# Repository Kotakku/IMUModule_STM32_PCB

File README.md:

# IMUModule_STM32_PCB

KiCad project to reproduce the contents of the following paper

H. Kamata, M. Kimishima, T. Sawada, Y. Suga, H. Takeda, K. Yamashita, and S. Mitani, MEMS Gyro Array Employing Array Signal Processing for Interference and Outlier Suppression, IEEE Inertial 2020, Hiroshima, Japan

## Firmware
[IMUModule_G473RC](https://github.com/Kotakku/IMUModule_G473RC)

## Board spec
- STM32G473RC
- LSM6DSR (x32)

## Requirements
- KiCad 8
- [KiCAD JLCPCB tools](https://github.com/bouni/kicad-jlcpcb-tools) (for JLCPCB PCBA)

## Production files
Use the files in ```jlcpcb/production_files```
- ```GERBER-IMUModule_STM32.zip```
- ```CPL-IMUModule_STM32.csv```
- ```BOM-IMUModule_STM32.csv```

## Images

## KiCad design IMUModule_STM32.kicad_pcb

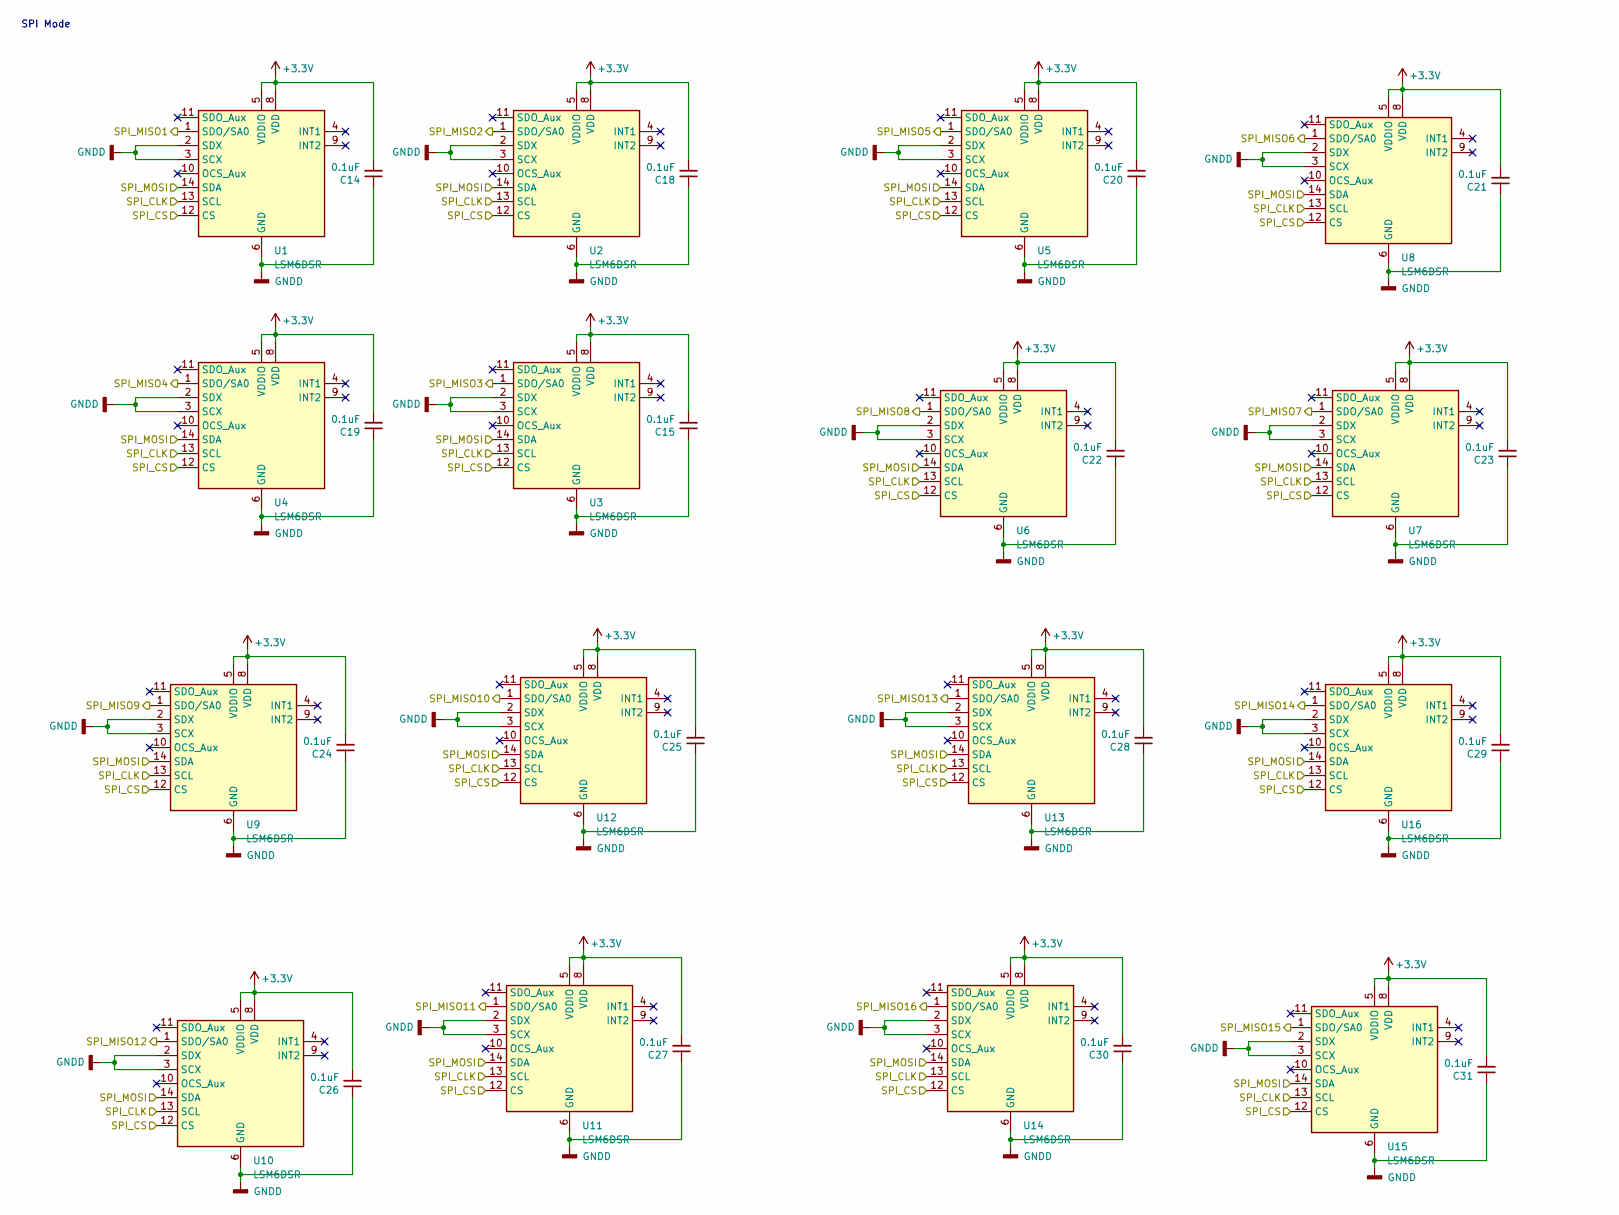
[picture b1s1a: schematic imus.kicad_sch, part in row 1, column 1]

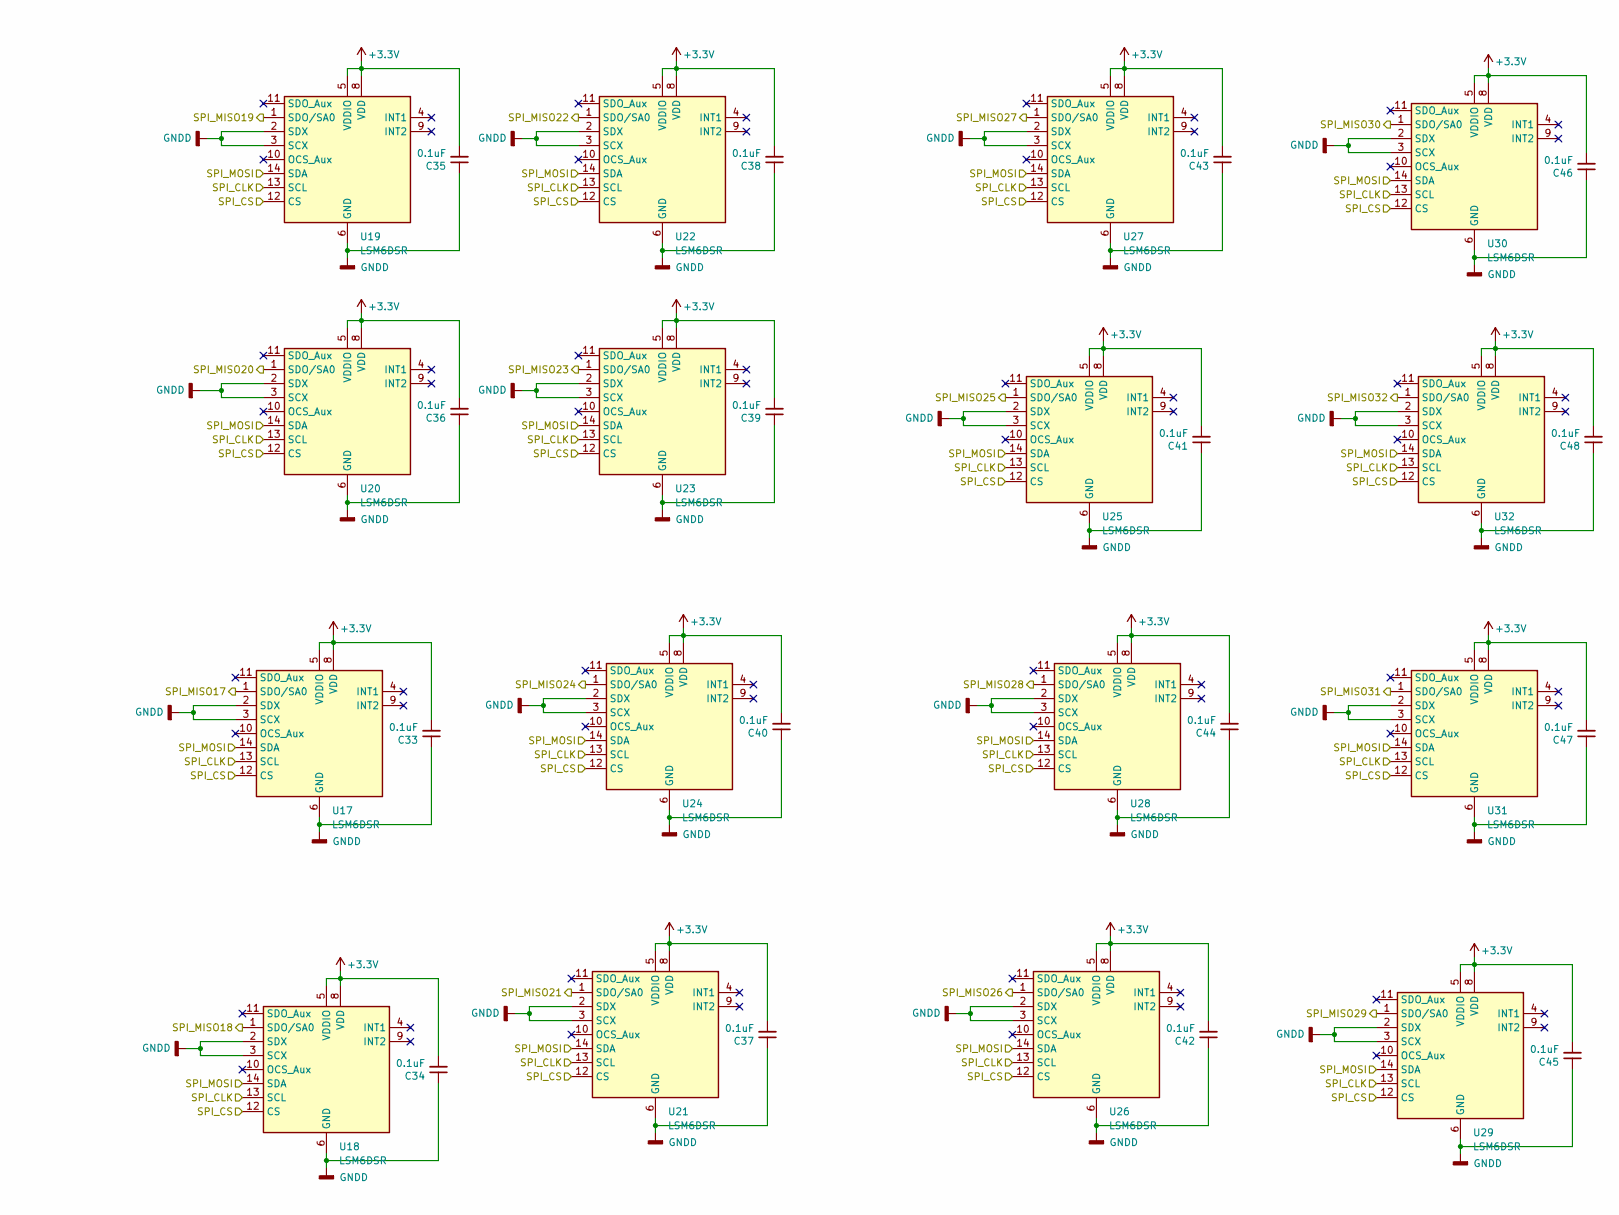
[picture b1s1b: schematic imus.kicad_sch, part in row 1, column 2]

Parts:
C14, C15, C18, C19, C20, C21, C22, C23, C24, C25, C26, C27, C28, C29, C30, C31, C33, C34, C35, C36, C37, C38, C39, C40, C41, C42, C43, C44, C45, C46, C47, C48: 0.1uF; C_0402_1005Metric
U1, U2, U3, U4, U5, U6, U7, U8, U9, U10, U11, U12, U13, U14, U15, U16, U17, U18, U19, U20, U21, U22, U23, U24, U25, U26, U27, U28, U29, U30, U31, U32: LSM6DSR; LGA-14_3x2.5mm_P0.5mm_LayoutBorder3x4y

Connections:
+3.3V: C14.2, C15.2, C18.2, C19.2, C20.2, C21.2, C22.2, C23.2, C24.2, C25.2, C26.2, C27.2, C28.2, C29.2, C30.2, C31.2, C33.2, C34.2, C35.2, C36.2, C37.2, C38.2, C39.2, C40.2, C41.2, C42.2, C43.2, C44.2, C45.2, C46.2, C47.2, C48.2, U1.5 (VDDIO), U1.8 (VDD), U2.5 (VDDIO), U2.8 (VDD), U3.5 (VDDIO), U3.8 (VDD), U4.5 (VDDIO), U4.8 (VDD), U5.5 (VDDIO), U5.8 (VDD), U6.5 (VDDIO), U6.8 (VDD), U7.5 (VDDIO), U7.8 (VDD), U8.5 (VDDIO), U8.8 (VDD), U9.5 (VDDIO), U9.8 (VDD), U10.5 (VDDIO), U10.8 (VDD), U11.5 (VDDIO), U11.8 (VDD), U12.5 (VDDIO), U12.8 (VDD), U13.5 (VDDIO), U13.8 (VDD), U14.5 (VDDIO), U14.8 (VDD), U15.5 (VDDIO), U15.8 (VDD), U16.5 (VDDIO), U16.8 (VDD), U17.5 (VDDIO), U17.8 (VDD), U18.5 (VDDIO), U18.8 (VDD), U19.5 (VDDIO), U19.8 (VDD), U20.5 (VDDIO), U20.8 (VDD), U21.5 (VDDIO), U21.8 (VDD), U22.5 (VDDIO), U22.8 (VDD), U23.5 (VDDIO), U23.8 (VDD), U24.5 (VDDIO), U24.8 (VDD), U25.5 (VDDIO), U25.8 (VDD), U26.5 (VDDIO), U26.8 (VDD), U27.5 (VDDIO), U27.8 (VDD), U28.5 (VDDIO), U28.8 (VDD), U29.5 (VDDIO), U29.8 (VDD), U30.5 (VDDIO), U30.8 (VDD), U31.5 (VDDIO), U31.8 (VDD), U32.5 (VDDIO), U32.8 (VDD); also elsewhere on the board
/IMUs/SPI_CLK: U1.13 (SCL), U2.13 (SCL), U3.13 (SCL), U4.13 (SCL), U5.13 (SCL), U6.13 (SCL), U7.13 (SCL), U8.13 (SCL), U9.13 (SCL), U10.13 (SCL), U11.13 (SCL), U12.13 (SCL), U13.13 (SCL), U14.13 (SCL), U15.13 (SCL), U16.13 (SCL), U17.13 (SCL), U18.13 (SCL), U19.13 (SCL), U20.13 (SCL), U21.13 (SCL), U22.13 (SCL), U23.13 (SCL), U24.13 (SCL), U25.13 (SCL), U26.13 (SCL), U27.13 (SCL), U28.13 (SCL), U29.13 (SCL), U30.13 (SCL), U31.13 (SCL), U32.13 (SCL); also elsewhere on the board
/IMUs/SPI_CS: U1.12 (CS), U2.12 (CS), U3.12 (CS), U4.12 (CS), U5.12 (CS), U6.12 (CS), U7.12 (CS), U8.12 (CS), U9.12 (CS), U10.12 (CS), U11.12 (CS), U12.12 (CS), U13.12 (CS), U14.12 (CS), U15.12 (CS), U16.12 (CS), U17.12 (CS), U18.12 (CS), U19.12 (CS), U20.12 (CS), U21.12 (CS), U22.12 (CS), U23.12 (CS), U24.12 (CS), U25.12 (CS), U26.12 (CS), U27.12 (CS), U28.12 (CS), U29.12 (CS), U30.12 (CS), U31.12 (CS), U32.12 (CS); also elsewhere on the board
/IMUs/SPI_MISO1: U1.1 (SDO/SA0); also elsewhere on the board
/IMUs/SPI_MISO2: U2.1 (SDO/SA0); also elsewhere on the board
/IMUs/SPI_MISO3: U3.1 (SDO/SA0); also elsewhere on the board
/IMUs/SPI_MISO4: U4.1 (SDO/SA0); also elsewhere on the board
/IMUs/SPI_MISO5: U5.1 (SDO/SA0); also elsewhere on the board
/IMUs/SPI_MISO6: U8.1 (SDO/SA0); also elsewhere on the board
/IMUs/SPI_MISO7: U7.1 (SDO/SA0); also elsewhere on the board
/IMUs/SPI_MISO8: U6.1 (SDO/SA0); also elsewhere on the board
/IMUs/SPI_MISO9: U9.1 (SDO/SA0); also elsewhere on the board
/IMUs/SPI_MISO10: U12.1 (SDO/SA0); also elsewhere on the board
/IMUs/SPI_MISO11: U11.1 (SDO/SA0); also elsewhere on the board
/IMUs/SPI_MISO12: U10.1 (SDO/SA0); also elsewhere on the board
/IMUs/SPI_MISO13: U13.1 (SDO/SA0); also elsewhere on the board
/IMUs/SPI_MISO14: U16.1 (SDO/SA0); also elsewhere on the board
/IMUs/SPI_MISO15: U15.1 (SDO/SA0); also elsewhere on the board
/IMUs/SPI_MISO16: U14.1 (SDO/SA0); also elsewhere on the board
/IMUs/SPI_MISO17: U17.1 (SDO/SA0); also elsewhere on the board
/IMUs/SPI_MISO18: U18.1 (SDO/SA0); also elsewhere on the board
/IMUs/SPI_MISO19: U19.1 (SDO/SA0); also elsewhere on the board
/IMUs/SPI_MISO20: U20.1 (SDO/SA0); also elsewhere on the board
/IMUs/SPI_MISO21: U21.1 (SDO/SA0); also elsewhere on the board
/IMUs/SPI_MISO22: U22.1 (SDO/SA0); also elsewhere on the board
/IMUs/SPI_MISO23: U23.1 (SDO/SA0); also elsewhere on the board
/IMUs/SPI_MISO24: U24.1 (SDO/SA0); also elsewhere on the board
/IMUs/SPI_MISO25: U25.1 (SDO/SA0); also elsewhere on the board
/IMUs/SPI_MISO26: U26.1 (SDO/SA0); also elsewhere on the board
/IMUs/SPI_MISO27: U27.1 (SDO/SA0); also elsewhere on the board
/IMUs/SPI_MISO28: U28.1 (SDO/SA0); also elsewhere on the board
/IMUs/SPI_MISO29: U29.1 (SDO/SA0); also elsewhere on the board
/IMUs/SPI_MISO30: U30.1 (SDO/SA0); also elsewhere on the board
/IMUs/SPI_MISO31: U31.1 (SDO/SA0); also elsewhere on the board
/IMUs/SPI_MISO32: U32.1 (SDO/SA0); also elsewhere on the board
/IMUs/SPI_MOSI: U1.14 (SDA), U2.14 (SDA), U3.14 (SDA), U4.14 (SDA), U5.14 (SDA), U6.14 (SDA), U7.14 (SDA), U8.14 (SDA), U9.14 (SDA), U10.14 (SDA), U11.14 (SDA), U12.14 (SDA), U13.14 (SDA), U14.14 (SDA), U15.14 (SDA), U16.14 (SDA), U17.14 (SDA), U18.14 (SDA), U19.14 (SDA), U20.14 (SDA), U21.14 (SDA), U22.14 (SDA), U23.14 (SDA), U24.14 (SDA), U25.14 (SDA), U26.14 (SDA), U27.14 (SDA), U28.14 (SDA), U29.14 (SDA), U30.14 (SDA), U31.14 (SDA), U32.14 (SDA); also elsewhere on the board
GNDD: C14.1, C15.1, C18.1, C19.1, C20.1, C21.1, C22.1, C23.1, C24.1, C25.1, C26.1, C27.1, C28.1, C29.1, C30.1, C31.1, C33.1, C34.1, C35.1, C36.1, C37.1, C38.1, C39.1, C40.1, C41.1, C42.1, C43.1, C44.1, C45.1, C46.1, C47.1, C48.1, U1.2 (SDX), U1.3 (SCX), U1.6 (GND), U1.7 (GND), U2.2 (SDX), U2.3 (SCX), U2.6 (GND), U2.7 (GND), U3.2 (SDX), U3.3 (SCX), U3.6 (GND), U3.7 (GND), U4.2 (SDX), U4.3 (SCX), U4.6 (GND), U4.7 (GND), U5.2 (SDX), U5.3 (SCX), U5.6 (GND), U5.7 (GND), U6.2 (SDX), U6.3 (SCX), U6.6 (GND), U6.7 (GND), U7.2 (SDX), U7.3 (SCX), U7.6 (GND), U7.7 (GND), U8.2 (SDX), U8.3 (SCX), U8.6 (GND), U8.7 (GND), U9.2 (SDX), U9.3 (SCX), U9.6 (GND), U9.7 (GND), U10.2 (SDX), U10.3 (SCX), U10.6 (GND), U10.7 (GND), U11.2 (SDX), U11.3 (SCX), U11.6 (GND), U11.7 (GND), U12.2 (SDX), U12.3 (SCX), U12.6 (GND), U12.7 (GND), U13.2 (SDX), U13.3 (SCX), U13.6 (GND), U13.7 (GND), U14.2 (SDX), U14.3 (SCX), U14.6 (GND), U14.7 (GND), U15.2 (SDX), U15.3 (SCX), U15.6 (GND), U15.7 (GND), U16.2 (SDX), U16.3 (SCX), U16.6 (GND), U16.7 (GND), U17.2 (SDX), U17.3 (SCX), U17.6 (GND), U17.7 (GND), U18.2 (SDX), U18.3 (SCX), U18.6 (GND), U18.7 (GND), U19.2 (SDX), U19.3 (SCX), U19.6 (GND), U19.7 (GND), U20.2 (SDX), U20.3 (SCX), U20.6 (GND), U20.7 (GND), U21.2 (SDX), U21.3 (SCX), U21.6 (GND), U21.7 (GND), U22.2 (SDX), U22.3 (SCX), U22.6 (GND), U22.7 (GND), U23.2 (SDX), U23.3 (SCX), U23.6 (GND), U23.7 (GND), U24.2 (SDX), U24.3 (SCX), U24.6 (GND), U24.7 (GND), U25.2 (SDX), U25.3 (SCX), U25.6 (GND), U25.7 (GND), U26.2 (SDX), U26.3 (SCX), U26.6 (GND), U26.7 (GND), U27.2 (SDX), U27.3 (SCX), U27.6 (GND), U27.7 (GND), U28.2 (SDX), U28.3 (SCX), U28.6 (GND), U28.7 (GND), U29.2 (SDX), U29.3 (SCX), U29.6 (GND), U29.7 (GND), U30.2 (SDX), U30.3 (SCX), U30.6 (GND), U30.7 (GND), U31.2 (SDX), U31.3 (SCX), U31.6 (GND), U31.7 (GND), U32.2 (SDX), U32.3 (SCX), U32.6 (GND), U32.7 (GND); also elsewhere on the board

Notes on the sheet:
SPI Mode

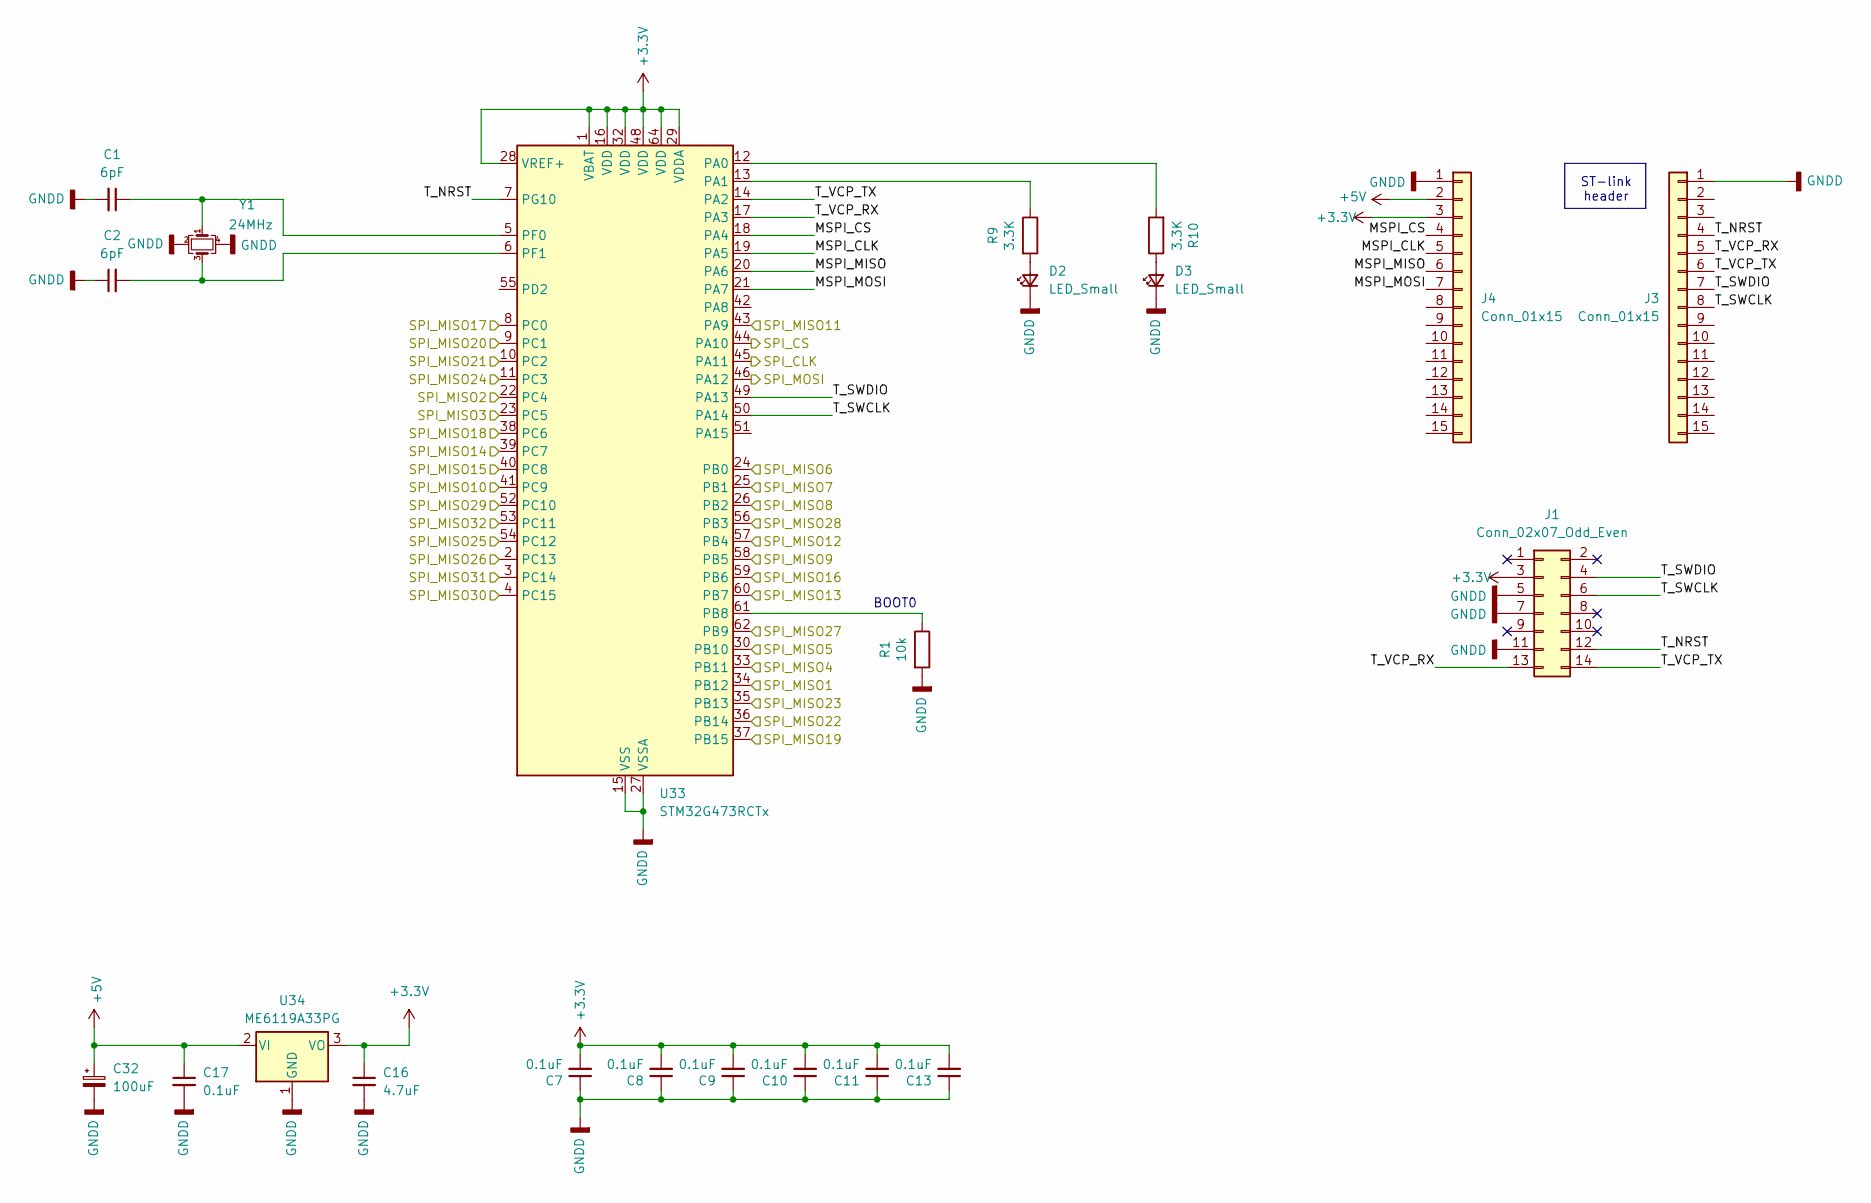
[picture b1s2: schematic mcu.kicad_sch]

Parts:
C1, C2: 6pF; C_0402_1005Metric
C7, C8, C9, C10, C11, C13, C17: 0.1uF; C_0402_1005Metric
C16: 4.7uF; C_0603_1608Metric
C32: 100uF; CP_EIA-3528-15_AVX-H
D2, D3: LED_Small; LED_0603_1608Metric
J1: Conn_02x07_Odd_Even; PinHeader_2x07_P1.27mm_Vertical_SMD
J3, J4: Conn_01x15; PinHeader_1x15_P2.54mm_Vertical
R1: 10k; R_0402_1005Metric
R9, R10: 3.3K; R_0402_1005Metric
U33: STM32G473RCTx; LQFP-64_10x10mm_P0.5mm
U34: ME6119A33PG; SOT-89-3
Y1: 24MHz; Crystal_SMD_2016-4Pin_2.0x1.6mm

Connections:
+3.3V: C7.2, C8.2, C9.2, C10.2, C11.2, C13.2, C16.1, J1.3, J4.3, U33.1 (VBAT), U33.16 (VDD), U33.28 (VREF+), U33.29 (VDDA), U33.32 (VDD), U33.48 (VDD), U33.64 (VDD), U34.3 (VO); also elsewhere on the board
+5V: C17.1, C32.1, J4.2, U34.2 (VI)
/IMUs/SPI_CLK: U33.45 (PA11); also elsewhere on the board
/IMUs/SPI_CS: U33.44 (PA10); also elsewhere on the board
/IMUs/SPI_MISO1: U33.34 (PB12); also elsewhere on the board
/IMUs/SPI_MISO2: U33.22 (PC4); also elsewhere on the board
/IMUs/SPI_MISO3: U33.23 (PC5); also elsewhere on the board
/IMUs/SPI_MISO4: U33.33 (PB11); also elsewhere on the board
/IMUs/SPI_MISO5: U33.30 (PB10); also elsewhere on the board
/IMUs/SPI_MISO6: U33.24 (PB0); also elsewhere on the board
/IMUs/SPI_MISO7: U33.25 (PB1); also elsewhere on the board
/IMUs/SPI_MISO8: U33.26 (PB2); also elsewhere on the board
/IMUs/SPI_MISO9: U33.58 (PB5); also elsewhere on the board
/IMUs/SPI_MISO10: U33.41 (PC9); also elsewhere on the board
/IMUs/SPI_MISO11: U33.43 (PA9); also elsewhere on the board
/IMUs/SPI_MISO12: U33.57 (PB4); also elsewhere on the board
/IMUs/SPI_MISO13: U33.60 (PB7); also elsewhere on the board
/IMUs/SPI_MISO14: U33.39 (PC7); also elsewhere on the board
/IMUs/SPI_MISO15: U33.40 (PC8); also elsewhere on the board
/IMUs/SPI_MISO16: U33.59 (PB6); also elsewhere on the board
/IMUs/SPI_MISO17: U33.8 (PC0); also elsewhere on the board
/IMUs/SPI_MISO18: U33.38 (PC6); also elsewhere on the board
/IMUs/SPI_MISO19: U33.37 (PB15); also elsewhere on the board
/IMUs/SPI_MISO20: U33.9 (PC1); also elsewhere on the board
/IMUs/SPI_MISO21: U33.10 (PC2); also elsewhere on the board
/IMUs/SPI_MISO22: U33.36 (PB14); also elsewhere on the board
/IMUs/SPI_MISO23: U33.35 (PB13); also elsewhere on the board
/IMUs/SPI_MISO24: U33.11 (PC3); also elsewhere on the board
/IMUs/SPI_MISO25: U33.54 (PC12); also elsewhere on the board
/IMUs/SPI_MISO26: U33.2 (PC13); also elsewhere on the board
/IMUs/SPI_MISO27: U33.62 (PB9); also elsewhere on the board
/IMUs/SPI_MISO28: U33.56 (PB3); also elsewhere on the board
/IMUs/SPI_MISO29: U33.52 (PC10); also elsewhere on the board
/IMUs/SPI_MISO30: U33.4 (PC15); also elsewhere on the board
/IMUs/SPI_MISO31: U33.3 (PC14); also elsewhere on the board
/IMUs/SPI_MISO32: U33.53 (PC11); also elsewhere on the board
/IMUs/SPI_MOSI: U33.46 (PA12); also elsewhere on the board
/MCU/MSPI_CLK: J4.5, U33.19 (PA5)
/MCU/MSPI_CS: J4.4, U33.18 (PA4)
/MCU/MSPI_MISO: J4.6, U33.20 (PA6)
/MCU/MSPI_MOSI: J4.7, U33.21 (PA7)
/MCU/T_NRST: J1.12, J3.4, U33.7 (PG10)
/MCU/T_SWCLK: J1.6, J3.8, U33.50 (PA14)
/MCU/T_SWDIO: J1.4, J3.7, U33.49 (PA13)
/MCU/T_VCP_RX: J1.13, J3.5, U33.17 (PA3)
/MCU/T_VCP_TX: J1.14, J3.6, U33.14 (PA2)
GNDD: C1.2, C2.1, C7.1, C8.1, C9.1, C10.1, C11.1, C13.1, C16.2, C17.2, C32.2, D2.1 (K), D3.1 (K), J1.5, J1.7, J1.11, J3.1, J4.1, R1.2, U33.15 (VSS), U33.27 (VSSA), U33.31 (VSS), U33.47 (VSS), U33.63 (VSS), U34.1 (GND), Y1.2, Y1.4; also elsewhere on the board
unnamed: D2.2 (A), R9.2
unnamed: D3.2 (A), R10.1
unnamed: R10.2, U33.12 (PA0)
unnamed: R9.1, U33.13 (PA1)
unnamed: R1.1, U33.61 (PB8)
unnamed: C1.1, U33.5 (PF0), Y1.1
unnamed: C2.2, U33.6 (PF1), Y1.3

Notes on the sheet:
ST-link header
BOOT0

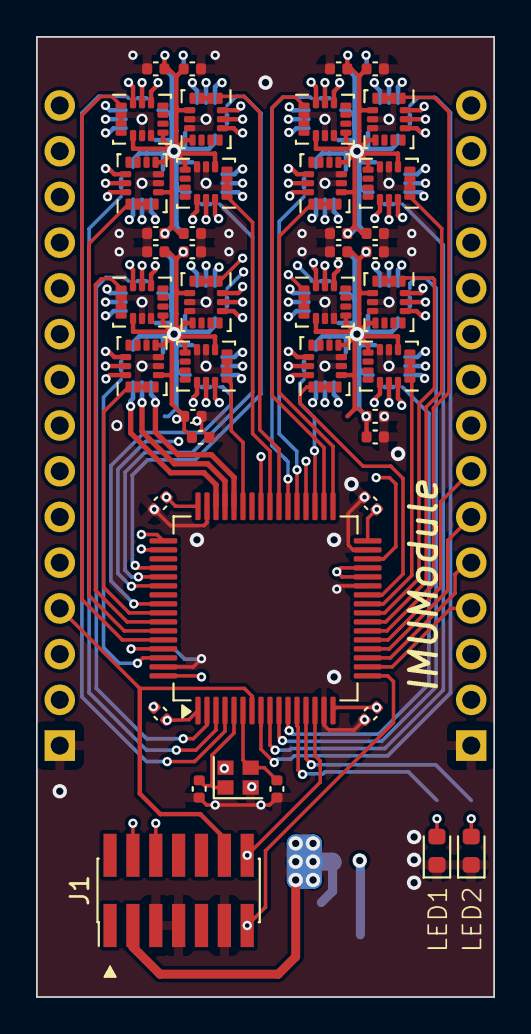
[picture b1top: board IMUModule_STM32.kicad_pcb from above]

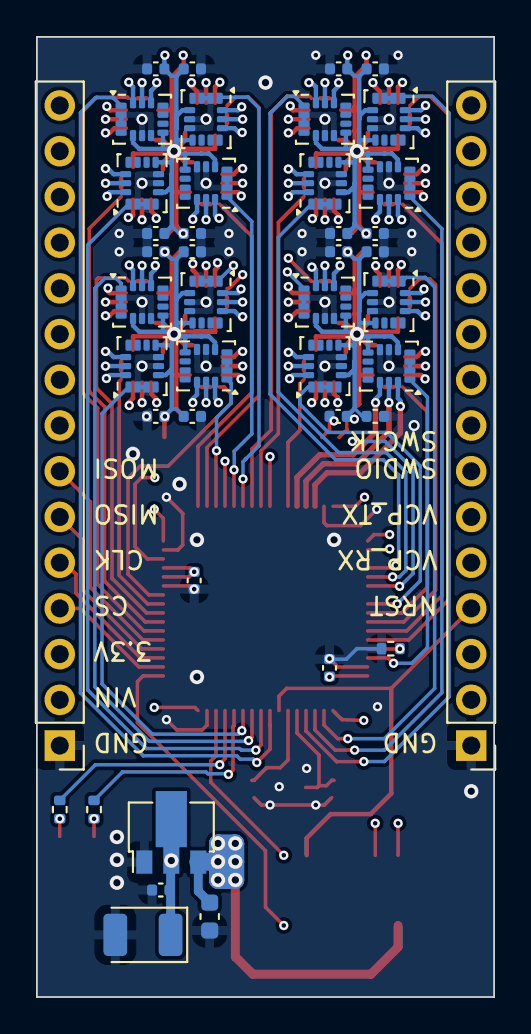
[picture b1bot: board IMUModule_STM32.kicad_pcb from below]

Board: 4 copper layers, 25.4 x 53.3 mm, 86 parts (43 on the bottom side), 54 nets.

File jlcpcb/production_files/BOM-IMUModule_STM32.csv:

Comment,Designator,Footprint,LCSC
0.1uF,"C10,C11,C13,C14,C15,C17,C18,C19,C20,C21,C22,C23,C24,C25,C26,C27,C28,C29,C30,C31,C33,C34,C35,C36,C37,C38,C39,C40,C41,C42,C43,C44,C45,C46,C47,C48,C7,C8,C9",C_0402_1005Metric,C1525
6pF,"C1,C2",C_0402_1005Metric,C1575
100uF,C32,CP_EIA-3528-15_AVX-H,C16133
4.7uF,C16,C_0603_1608Metric,C19666
24MHz,Y1,Crystal_SMD_2016-4Pin_2.0x1.6mm,C1985381
LED_Small,"D2,D3",LED_0603_1608Metric,C2286
10k,R1,R_0402_1005Metric,C25744
3.3K,"R10,R9",R_0402_1005Metric,C25890
Conn_02x07_Odd_Even,J1,PinHeader_2x07_P1.27mm_Vertical_SMD,C2881912
STM32G473RCTx,U33,LQFP-64_10x10mm_P0.5mm,C529361
LSM6DSR,"U1,U10,U11,U12,U13,U14,U15,U16,U17,U18,U19,U2,U20,U21,U22,U23,U24,U25,U26,U27,U28,U29,U3,U30,U31,U32,U4,U5,U6,U7,U8,U9",LGA-14_3x2.5mm_P0.5mm_LayoutBorder3x4y,C784817
ME6119A33PG,U34,SOT-89-3,C82566

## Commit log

2024-08-04 Add firmware repo to README
